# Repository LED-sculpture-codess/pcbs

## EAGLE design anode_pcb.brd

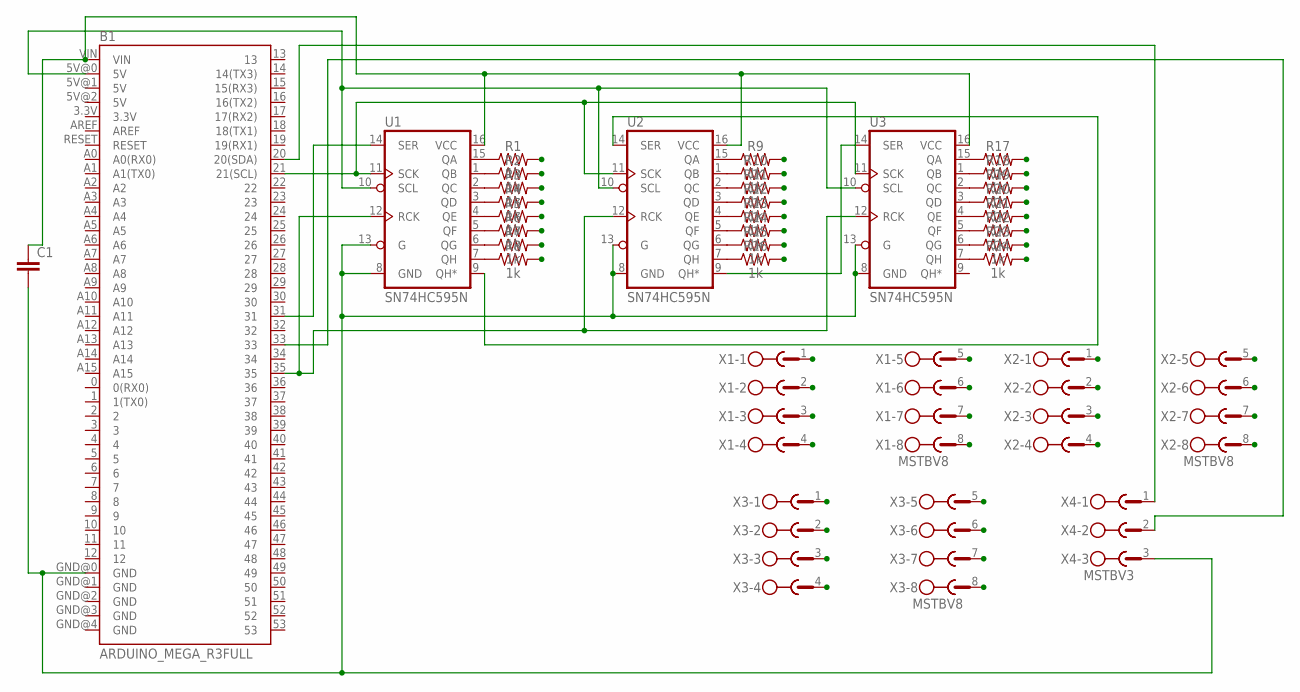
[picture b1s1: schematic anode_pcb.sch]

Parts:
B1: ARDUINO_MEGA_R3FULL; ARDUINO_MEGA
C1: C2.5/2; C2.5-2
R1, R2, R3, R4, R5, R6, R7, R8, R9, R10, R11, R12, R13, R14, R15, R16, R17, R18, R19, R20, R21, R22, R23, R24: 1k; AXIAL-0.3
U1, U2, U3: SN74HC595N; DIP16
X1, X2, X3: MSTBV8
X4: MSTBV3

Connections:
A1: R1.P$2 (2), X1.1
A2: R2.P$2 (2), X1.2
A3: R3.P$2 (2), X1.3
A4: R4.P$2 (2), X1.4
A5: R5.P$2 (2), X1.5
A6: R6.P$2 (2), X1.6
A7: R7.P$2 (2), X1.7
A8: R8.P$2 (2), X1.8
A9: R9.P$2 (2), X2.1
A10: R10.P$2 (2), X2.2
A11: R11.P$2 (2), X2.3
A12: R12.P$2 (2), X2.4
A13: R13.P$2 (2), X2.5
A14: R14.P$2 (2), X2.6
A15: R15.P$2 (2), X2.7
A16: R16.P$2 (2), X2.8
A17: R17.P$2 (2), X3.1
A18: R18.P$2 (2), X3.2
A19: R19.P$2 (2), X3.3
A20: R20.P$2 (2), X3.4
A21: R21.P$2 (2), X3.5
A22: R22.P$2 (2), X3.6
A23: R23.P$2 (2), X3.7
A24: R24.P$2 (2), X3.8
unnamed: B1.5V@0 (5V), U1.10 (SCL), U2.10 (SCL), U3.10 (SCL)
unnamed: R1.P$1 (1), U1.15 (QA)
unnamed: B1.GND@0 (GND), C1.2, U1.8 (GND), U1.13 (G), U2.8 (GND), U2.13 (G), U3.8 (GND), U3.13 (G), X4.3
unnamed: R2.P$1 (1), U1.1 (QB)
unnamed: R4.P$1 (1), U1.3 (QD)
unnamed: R5.P$1 (1), U1.4 (QE)
unnamed: R6.P$1 (1), U1.5 (QF)
unnamed: R3.P$1 (1), U1.2 (QC)
unnamed: R7.P$1 (1), U1.6 (QG)
unnamed: R8.P$1 (1), U1.7 (QH)
unnamed: B1.20 (20(SDA)), X4.1
unnamed: B1.21 (21(SCL)), X4.2
unnamed: R9.P$1 (1), U2.15 (QA)
unnamed: R10.P$1 (1), U2.1 (QB)
unnamed: R11.P$1 (1), U2.2 (QC)
unnamed: R12.P$1 (1), U2.3 (QD)
unnamed: R13.P$1 (1), U2.4 (QE)
unnamed: R14.P$1 (1), U2.5 (QF)
unnamed: R15.P$1 (1), U2.6 (QG)
unnamed: R16.P$1 (1), U2.7 (QH)
unnamed: R17.P$1 (1), U3.15 (QA)
unnamed: R18.P$1 (1), U3.1 (QB)
unnamed: R19.P$1 (1), U3.2 (QC)
unnamed: R20.P$1 (1), U3.3 (QD)
unnamed: R21.P$1 (1), U3.4 (QE)
unnamed: R22.P$1 (1), U3.5 (QF)
unnamed: R23.P$1 (1), U3.6 (QG)
unnamed: R24.P$1 (1), U3.7 (QH)
unnamed: B1.33, U1.11 (SCK), U2.11 (SCK), U3.11 (SCK)
unnamed: U2.9 (QH*), U3.14 (SER)
unnamed: U1.9 (QH*), U2.14 (SER)
unnamed: B1.31, U1.14 (SER)
unnamed: B1.35, U1.12 (RCK), U2.12 (RCK), U3.12 (RCK)
unnamed: B1.VIN, C1.1, U1.16 (VCC), U2.16 (VCC), U3.16 (VCC)

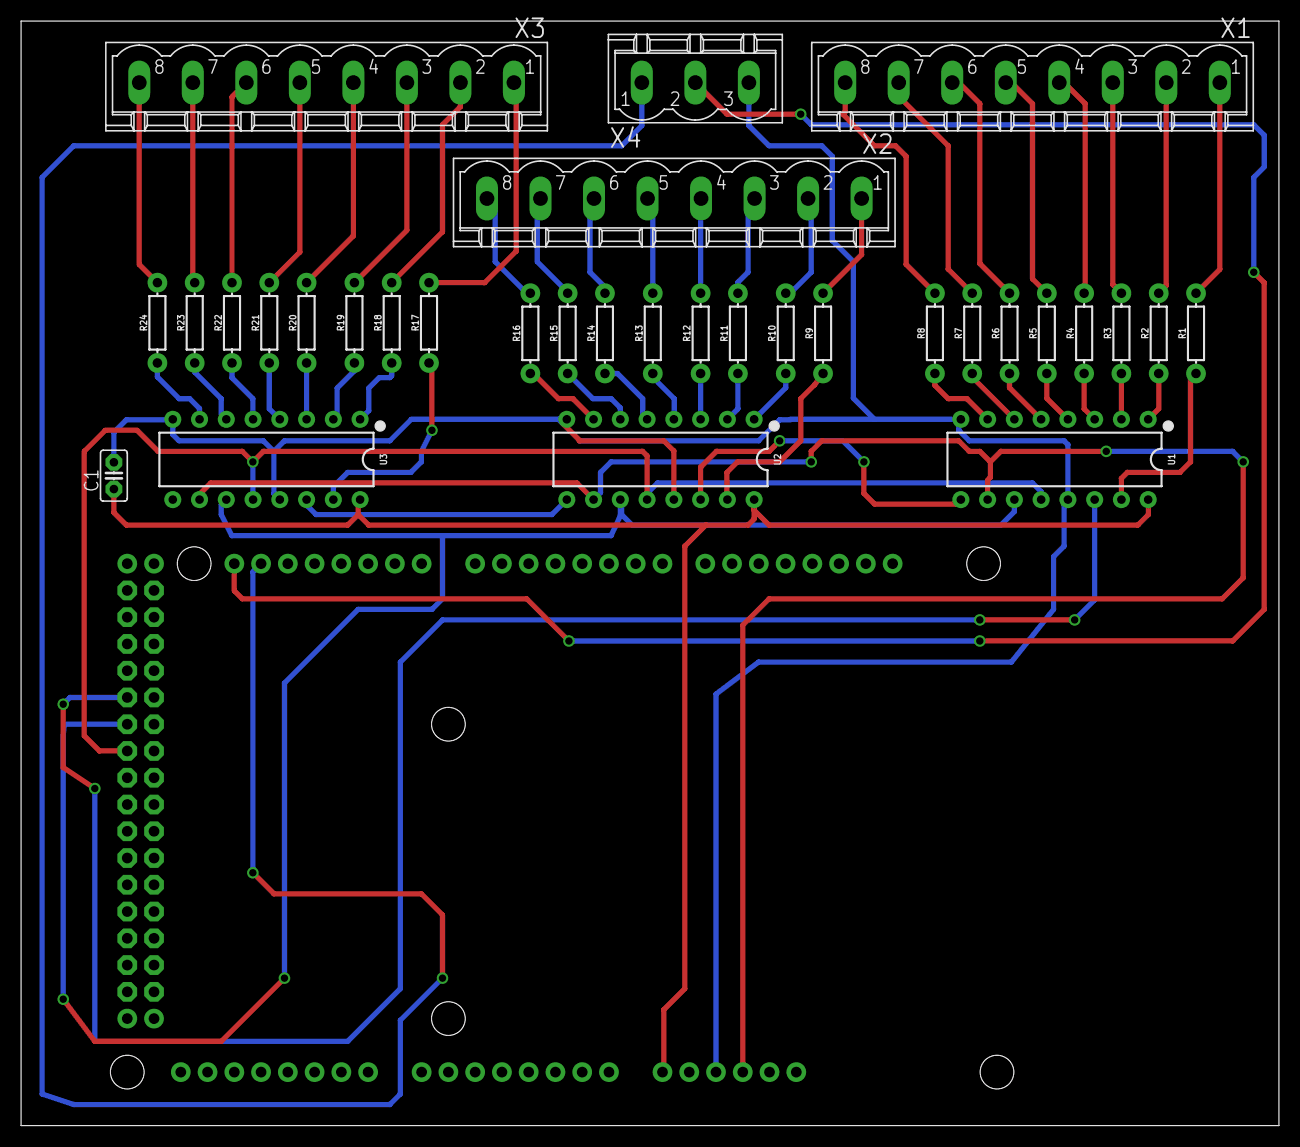
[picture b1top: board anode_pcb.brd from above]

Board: 2 copper layers, 119.4 x 104.8 mm, 33 parts (1 on the bottom side), 58 nets.

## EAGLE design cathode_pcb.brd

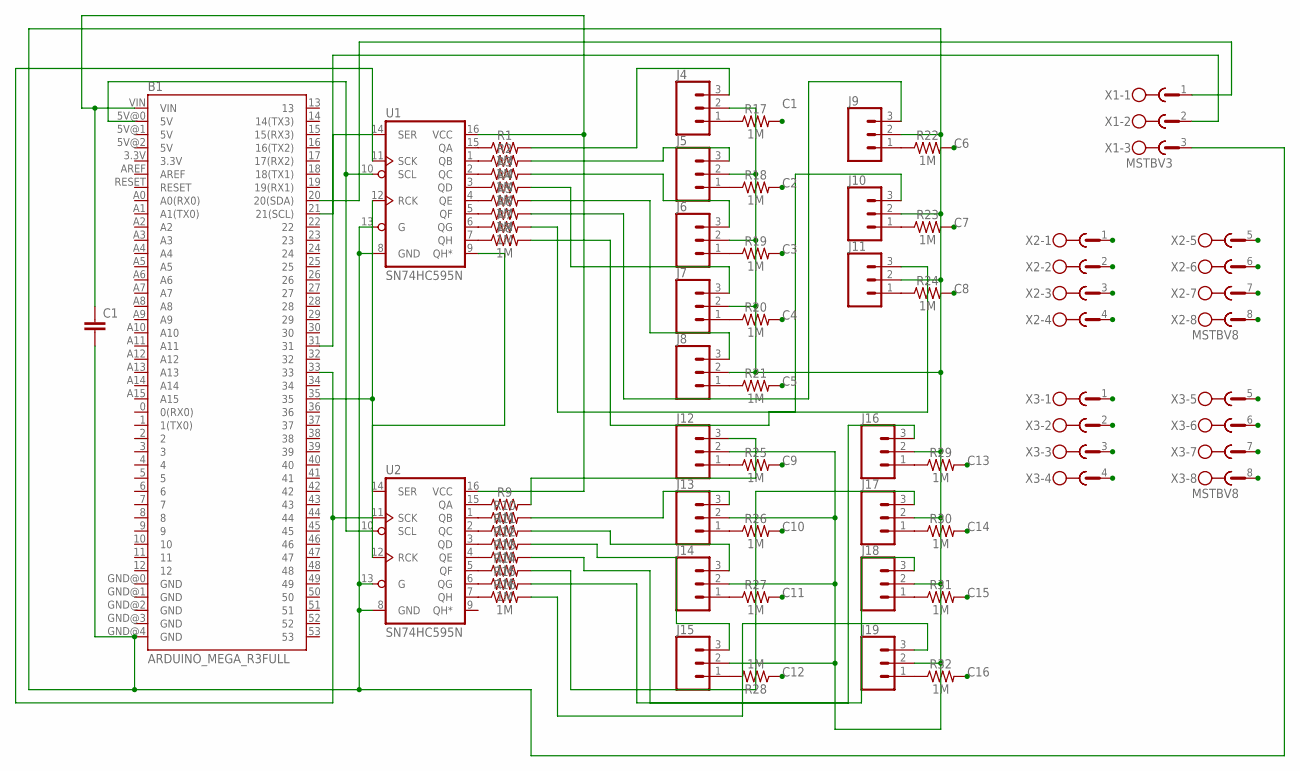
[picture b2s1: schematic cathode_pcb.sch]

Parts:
B1: ARDUINO_MEGA_R3FULL; ARDUINO_MEGA
C1: C2.5/2; C2.5-2
J4, J5, J6, J7, J8, J9, J10, J11, J12, J13, J14, J15, J16, J17, J18, J19: CONN_03; 1X03
R1, R2, R3, R4, R5, R6, R7, R8, R9, R10, R11, R12, R13, R14, R15, R16, R17, R18, R19, R20, R21, R22, R23, R24, R25, R26, R27, R28, R29, R30, R31, R32: 1M; AXIAL-0.3
U1, U2: SN74HC595N; DIP16
X1: MSTBV3
X2, X3: MSTBV8

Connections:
C1: R17.P$2 (2), X2.1
C2: R18.P$2 (2), X2.2
C3: R19.P$2 (2), X2.3
C4: R20.P$2 (2), X2.4
C5: R21.P$2 (2), X2.5
C6: R22.P$2 (2), X2.6
C7: R23.P$2 (2), X2.7
C8: R24.P$2 (2), X2.8
C9: R25.P$2 (2), X3.1
C10: R26.P$2 (2), X3.2
C11: R27.P$2 (2), X3.3
C12: R28.P$1 (1), X3.4
C13: R29.P$2 (2), X3.5
C14: R30.P$2 (2), X3.6
C15: R31.P$2 (2), X3.7
C16: R32.P$2 (2), X3.8
unnamed: J4.3, R1.P$2 (2)
unnamed: J5.3, R2.P$2 (2)
unnamed: R1.P$1 (1), U1.15 (QA)
unnamed: R2.P$1 (1), U1.1 (QB)
unnamed: R3.P$1 (1), U1.2 (QC)
unnamed: R4.P$1 (1), U1.3 (QD)
unnamed: R5.P$1 (1), U1.4 (QE)
unnamed: R6.P$1 (1), U1.5 (QF)
unnamed: R7.P$1 (1), U1.6 (QG)
unnamed: R8.P$1 (1), U1.7 (QH)
unnamed: R9.P$1 (1), U2.15 (QA)
unnamed: R10.P$1 (1), U2.1 (QB)
unnamed: R11.P$1 (1), U2.2 (QC)
unnamed: R12.P$1 (1), U2.3 (QD)
unnamed: R13.P$1 (1), U2.4 (QE)
unnamed: R14.P$1 (1), U2.5 (QF)
unnamed: R15.P$1 (1), U2.6 (QG)
unnamed: R16.P$1 (1), U2.7 (QH)
unnamed: J6.3, R3.P$2 (2)
unnamed: J7.3, R4.P$2 (2)
unnamed: J8.3, R5.P$2 (2)
unnamed: J9.3, R6.P$2 (2)
unnamed: J10.3, R7.P$2 (2)
unnamed: J11.3, R8.P$2 (2)
unnamed: J12.3, R9.P$2 (2)
unnamed: J13.3, R10.P$2 (2)
unnamed: J14.3, R11.P$2 (2)
unnamed: J15.3, R12.P$2 (2)
unnamed: J16.3, R13.P$2 (2)
unnamed: U1.9 (QH*), U2.14 (SER)
unnamed: J17.3, R14.P$2 (2)
unnamed: J18.3, R15.P$2 (2)
unnamed: J19.3, R16.P$2 (2)
unnamed: B1.5V@0 (5V), U1.10 (SCL), U2.10 (SCL)
unnamed: B1.31, U1.14 (SER)
unnamed: B1.GND@4 (GND), C1.2, J4.2, J5.2, J6.2, J7.2, J8.2, J9.2, J10.2, J11.2, J12.2, J13.2, J14.2, J15.2, J16.2, J17.2, J18.2, J19.2, U1.8 (GND), U1.13 (G), U2.8 (GND), U2.13 (G), X1.3
unnamed: B1.35, U1.12 (RCK), U2.12 (RCK)
unnamed: B1.33, U1.11 (SCK), U2.11 (SCK)
unnamed: J19.1, R32.P$1 (1)
unnamed: J18.1, R31.P$1 (1)
unnamed: J17.1, R30.P$1 (1)
unnamed: J16.1, R29.P$1 (1)
unnamed: J15.1, R28.P$2 (2)
unnamed: J14.1, R27.P$1 (1)
unnamed: J13.1, R26.P$1 (1)
unnamed: J12.1, R25.P$1 (1)
unnamed: J11.1, R24.P$1 (1)
unnamed: J10.1, R23.P$1 (1)
unnamed: J9.1, R22.P$1 (1)
unnamed: J4.1, R17.P$1 (1)
unnamed: J5.1, R18.P$1 (1)
unnamed: J6.1, R19.P$1 (1)
unnamed: J7.1, R20.P$1 (1)
unnamed: J8.1, R21.P$1 (1)
unnamed: B1.20 (20(SDA)), X1.1
unnamed: B1.21 (21(SCL)), X1.2
unnamed: B1.VIN, C1.1, U1.16 (VCC), U2.16 (VCC)

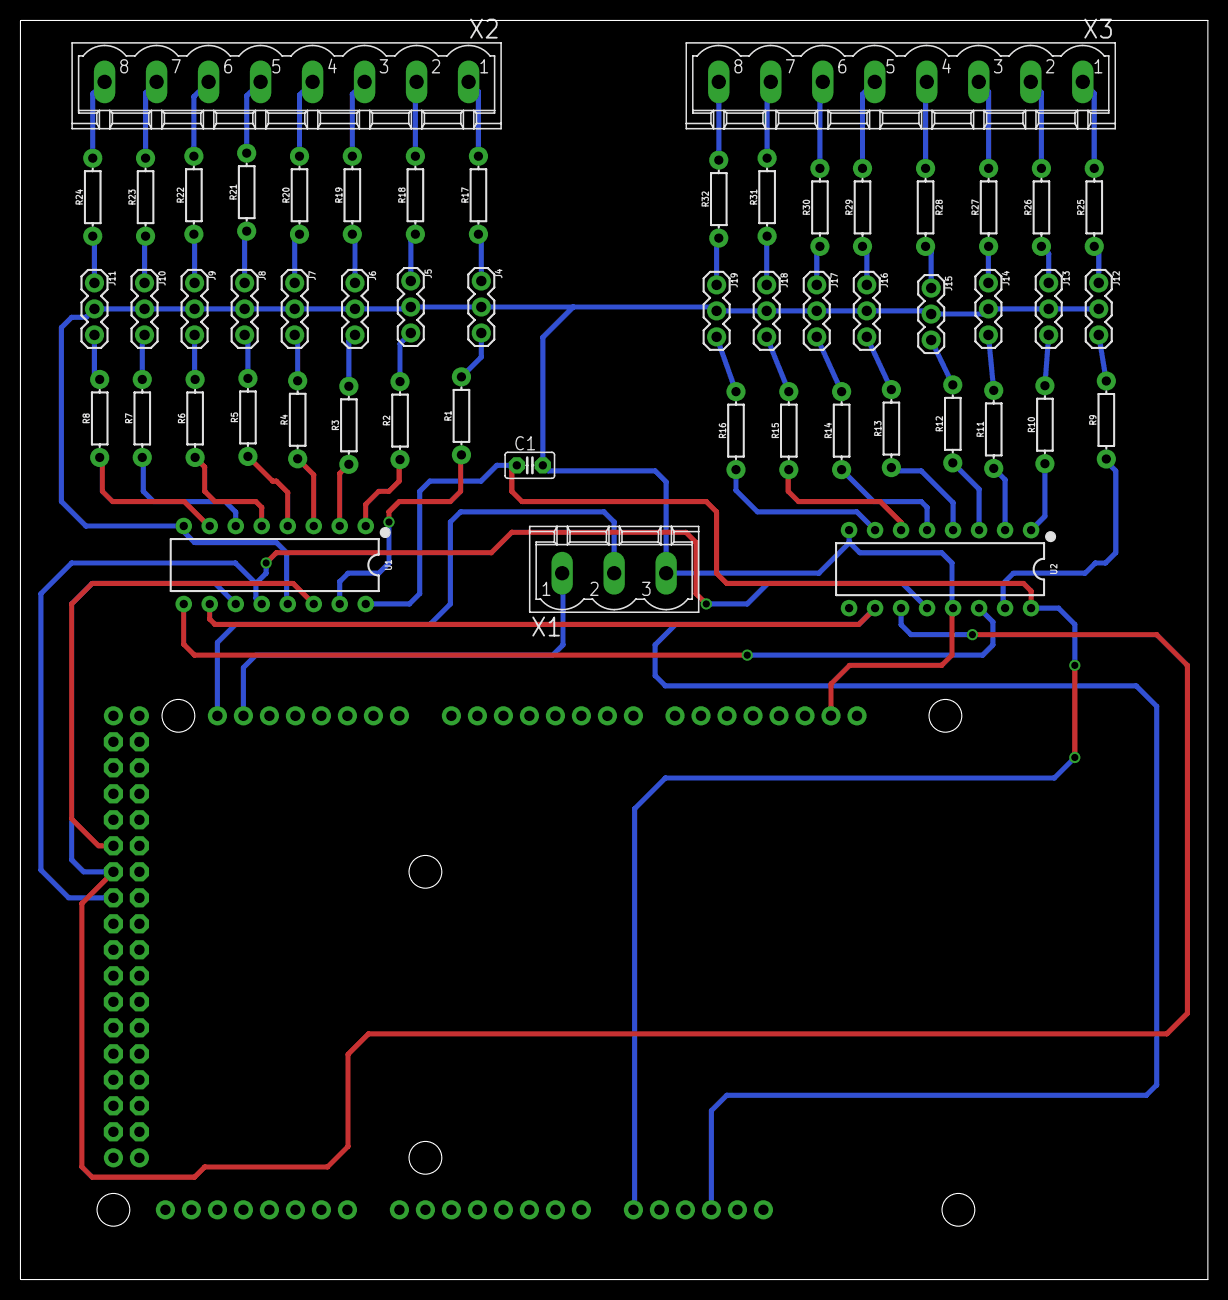
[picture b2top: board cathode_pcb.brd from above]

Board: 2 copper layers, 116.0 x 123.0 mm, 55 parts (1 on the bottom side), 73 nets.

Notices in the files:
parts and their libraries:
SparkFun-Boards: Licensing: Creative Commons ShareAlike 4.0 International - https://creativecommons.org/licenses/by-sa/4.0
